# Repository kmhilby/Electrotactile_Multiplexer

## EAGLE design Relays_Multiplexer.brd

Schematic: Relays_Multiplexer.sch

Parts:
C1, C2: 10uF/6.3V; CAPC1005X55_SMD-0402
IC1, IC2: PCA9685; SOP65P650X110-28
J1, J3, J4: PTH VERT FEMALE; HDRVR2W64P254_1X2_558X254X850B
J2: 1x33 Molex Connector; _MOLEX-5025983393_FPC_PITCH-0.3MM
J5: 2x17 PTH RA FEMALE; 2X17-RA-FEMALE
R1, R2, R3, R4, R5, R6, R7, R8, R11, R12, R13, R14, R15, R16, R17, R18: 10K; RESC1005X35_SMD-0402
R9, R10, R19, R21, R22, R23, R24, R25, R26, R27, R28, R29, R30, R31, R32, R33, R34, R35, R36, R37, R38, R39, R40, R41, R42, R43, R44, R45, R46, R47, R48, R49: 1K; RESC1005X35_SMD-0402
RELAY1, RELAY2, RELAY3, RELAY4, RELAY5, RELAY6, RELAY7, RELAY8, RELAY10, RELAY11, RELAY12, RELAY13, RELAY14, RELAY15, RELAY16, RELAY17, RELAY18, RELAY19, RELAY20, RELAY21, RELAY22, RELAY23, RELAY24, RELAY25, RELAY26, RELAY27, RELAY28, RELAY29, RELAY30, RELAY31, RELAY32, RELAY33: SPST-NO 170mA 250V; SOP254P609X203-4

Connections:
AGND: J2.P$33 (33), J3.2
AVCC: J3.1, RELAY1.4, RELAY2.4, RELAY3.4, RELAY4.4, RELAY5.4, RELAY6.4, RELAY7.4, RELAY8.4, RELAY10.4, RELAY11.4, RELAY12.4, RELAY13.4, RELAY14.4, RELAY15.4, RELAY16.4, RELAY17.4, RELAY18.4, RELAY19.4, RELAY20.4, RELAY21.4, RELAY22.4, RELAY23.4, RELAY24.4, RELAY25.4, RELAY26.4, RELAY27.4, RELAY28.4, RELAY29.4, RELAY30.4, RELAY31.4, RELAY32.4, RELAY33.4
GND: C1.2, C2.2, IC1.14 (GND), IC1.25 (EXTCLK), IC2.14 (GND), IC2.25 (EXTCLK), J4.2, J5.33, J5.34, R1.2, R2.2, R3.2, R5.2, R6.2, R7.2, R8.2, R9.1, R10.1, R11.2, R12.2, R13.2, R14.2, R15.2, R16.2, R17.2, R19.1, R21.1, R22.1, R23.1, R24.1, R25.1, R26.1, R27.1, R28.1, R29.1, R30.1, R31.1, R32.1, R33.1, R34.1, R35.1, R36.1, R37.1, R38.1, R39.1, R40.1, R41.1, R42.1, R43.1, R44.1, R45.1, R46.1, R47.1, R48.1, R49.1
unnamed: IC1.23 (!OE), R3.1
unnamed: IC1.4 (A3), R7.1
unnamed: IC1.24 (A5), R11.1
unnamed: IC1.5 (A4), R8.1
unnamed: IC1.3 (A2), R6.1
unnamed: IC1.2 (A1), R5.1
unnamed: IC2.1 (A0), R12.1
unnamed: IC2.3 (A2), R13.1
unnamed: IC2.4 (A3), R14.1
unnamed: IC2.5 (A4), R15.1
unnamed: IC2.24 (A5), R16.1
unnamed: IC2.23 (!OE), R1.1
unnamed: J2.P$17 (17), RELAY18.3
unnamed: J2.P$16 (16), RELAY17.3
unnamed: J2.P$15 (15), RELAY16.3
unnamed: J2.P$14 (14), RELAY15.3
unnamed: J2.P$13 (13), RELAY14.3
unnamed: J2.P$12 (12), RELAY13.3
unnamed: J2.P$11 (11), RELAY12.3
unnamed: J2.P$10 (10), RELAY11.3
unnamed: J2.P$9 (9), RELAY4.3
unnamed: J2.P$8 (8), RELAY3.3
unnamed: J2.P$7 (7), RELAY2.3
unnamed: J2.P$6 (6), RELAY1.3
unnamed: J2.P$5 (5), RELAY5.3
unnamed: J2.P$4 (4), RELAY6.3
unnamed: J2.P$3 (3), RELAY7.3
unnamed: J2.P$2 (2), RELAY8.3
unnamed: J2.P$1 (1), RELAY10.3
unnamed: J2.P$18 (18), RELAY19.3
unnamed: J2.P$19 (19), RELAY20.3
unnamed: J2.P$20 (20), RELAY21.3
unnamed: J2.P$21 (21), RELAY22.3
unnamed: J2.P$22 (22), RELAY23.3
unnamed: J2.P$23 (23), RELAY24.3
unnamed: J2.P$24 (24), RELAY25.3
unnamed: J2.P$25 (25), RELAY26.3
unnamed: J2.P$26 (26), RELAY27.3
unnamed: J2.P$27 (27), RELAY28.3
unnamed: J2.P$28 (28), RELAY29.3
unnamed: J2.P$29 (29), RELAY30.3
unnamed: J2.P$30 (30), RELAY31.3
unnamed: J2.P$31 (31), RELAY32.3
unnamed: J2.P$32 (32), RELAY33.3
unnamed: R19.2, RELAY7.2
unnamed: R21.2, RELAY6.2
unnamed: R9.2, RELAY10.2
unnamed: R10.2, RELAY8.2
unnamed: R22.2, RELAY5.2
unnamed: R23.2, RELAY1.2
unnamed: R24.2, RELAY2.2
unnamed: R25.2, RELAY3.2
unnamed: R26.2, RELAY4.2
unnamed: R27.2, RELAY11.2
unnamed: R28.2, RELAY12.2
unnamed: R29.2, RELAY13.2
unnamed: R30.2, RELAY14.2
unnamed: R31.2, RELAY15.2
unnamed: R32.2, RELAY16.2
unnamed: R33.2, RELAY17.2
unnamed: R34.2, RELAY18.2
unnamed: R35.2, RELAY19.2
unnamed: R36.2, RELAY20.2
unnamed: R37.2, RELAY21.2
unnamed: R38.2, RELAY22.2
unnamed: R39.2, RELAY23.2
unnamed: R40.2, RELAY24.2
unnamed: R41.2, RELAY25.2
unnamed: R42.2, RELAY26.2
unnamed: R43.2, RELAY27.2
unnamed: R44.2, RELAY28.2
unnamed: R45.2, RELAY29.2
unnamed: R46.2, RELAY30.2
unnamed: R47.2, RELAY31.2
unnamed: R48.2, RELAY32.2
unnamed: R49.2, RELAY33.2
SCL: IC1.26 (SCL), IC2.26 (SCL), J1.2, R18.1
SDA: IC1.27 (SDA), IC2.27 (SDA), J1.1, R4.2
SW: IC1.18 (PWM11), J5.12, RELAY13.1
SW1: IC1.6 (PWM0), J5.1, RELAY10.1
SW2: IC1.7 (PWM1), J5.2, RELAY8.1
SW3: IC1.8 (PWM2), J5.3, RELAY7.1
SW4: IC1.9 (PWM3), J5.4, RELAY6.1
SW5: IC1.10 (PWM4), J5.5, RELAY5.1
SW6: IC1.11 (PWM5), J5.6, RELAY1.1
SW7: IC1.12 (PWM6), J5.7, RELAY2.1
SW8: IC1.13 (PWM7), J5.8, RELAY3.1
SW9: IC1.15 (PWM8), J5.9, RELAY4.1
SW10: IC1.16 (PWM9), J5.10, RELAY11.1
SW11: IC1.17 (PWM10), J5.11, RELAY12.1
SW13: IC1.19 (PWM12), J5.13, RELAY14.1
SW14: IC1.20 (PWM13), J5.14, RELAY15.1
SW15: IC1.21 (PWM14), J5.15, RELAY16.1
SW16: IC1.22 (PWM15), J5.16, RELAY17.1
SW17: IC2.6 (PWM0), J5.17, RELAY18.1
SW18: IC2.7 (PWM1), J5.18, RELAY19.1
SW19: IC2.8 (PWM2), J5.19, RELAY20.1
SW20: IC2.9 (PWM3), J5.20, RELAY21.1
SW21: IC2.10 (PWM4), J5.21, RELAY22.1
SW22: IC2.11 (PWM5), J5.22, RELAY23.1
SW23: IC2.12 (PWM6), J5.23, RELAY24.1
SW24: IC2.13 (PWM7), J5.24, RELAY25.1
SW25: IC2.15 (PWM8), J5.25, RELAY26.1
SW26: IC2.16 (PWM9), J5.26, RELAY27.1
SW27: IC2.17 (PWM10), J5.27, RELAY28.1
SW28: IC2.18 (PWM11), J5.28, RELAY29.1
SW29: IC2.19 (PWM12), J5.29, RELAY30.1
SW30: IC2.20 (PWM13), J5.30, RELAY31.1
SW31: IC2.21 (PWM14), J5.31, RELAY32.1
SW32: IC2.22 (PWM15), J5.32, RELAY33.1
VCC: C1.1, C2.1, IC1.1 (A0), IC1.28 (VCC), IC2.2 (A1), IC2.28 (VCC), J4.1, R2.1, R4.1, R17.1, R18.2

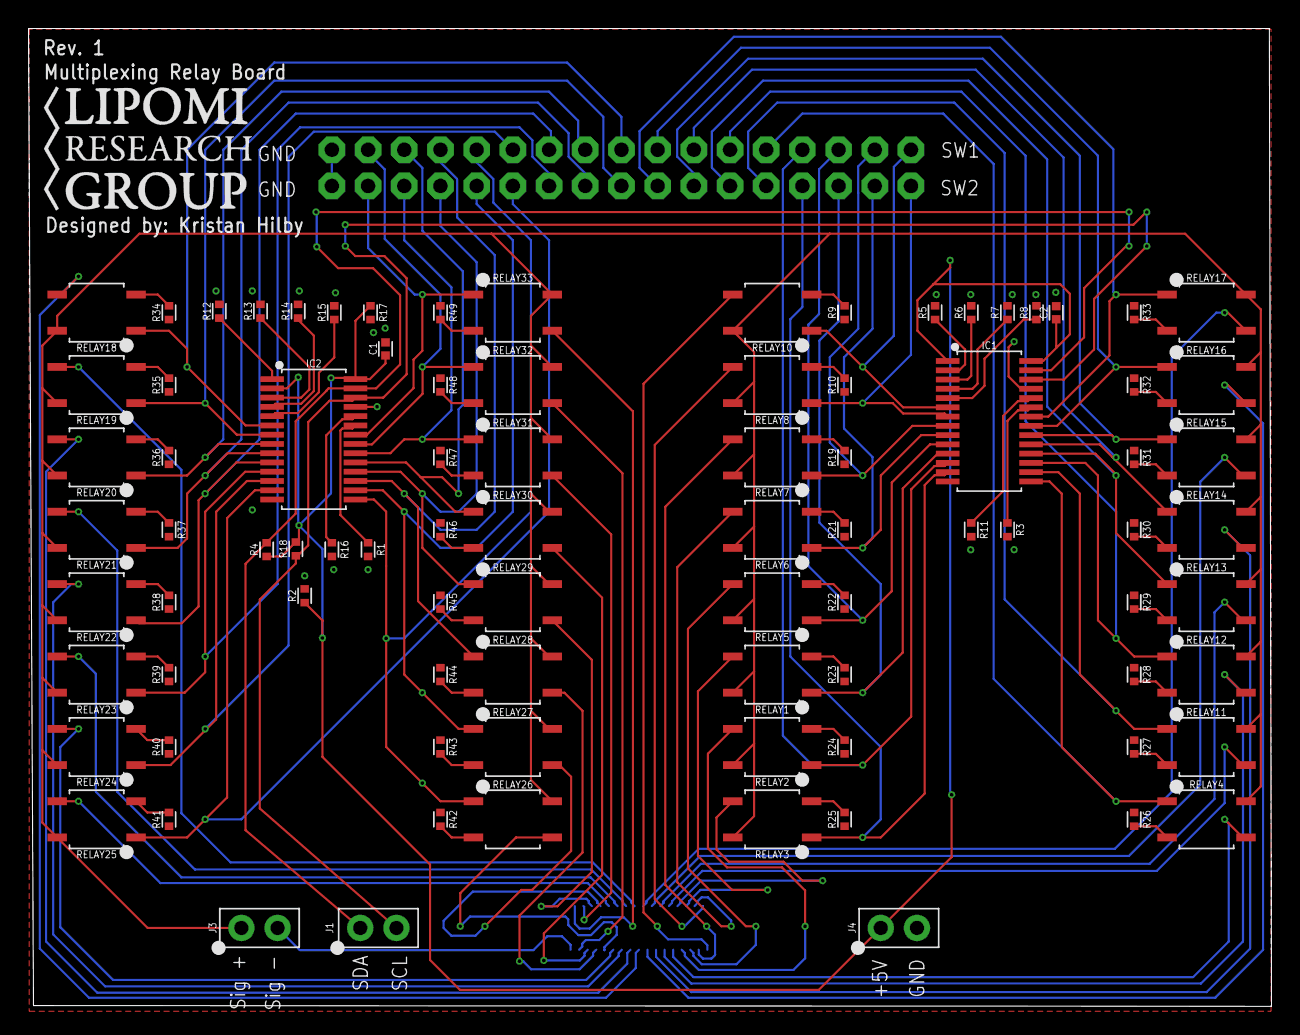
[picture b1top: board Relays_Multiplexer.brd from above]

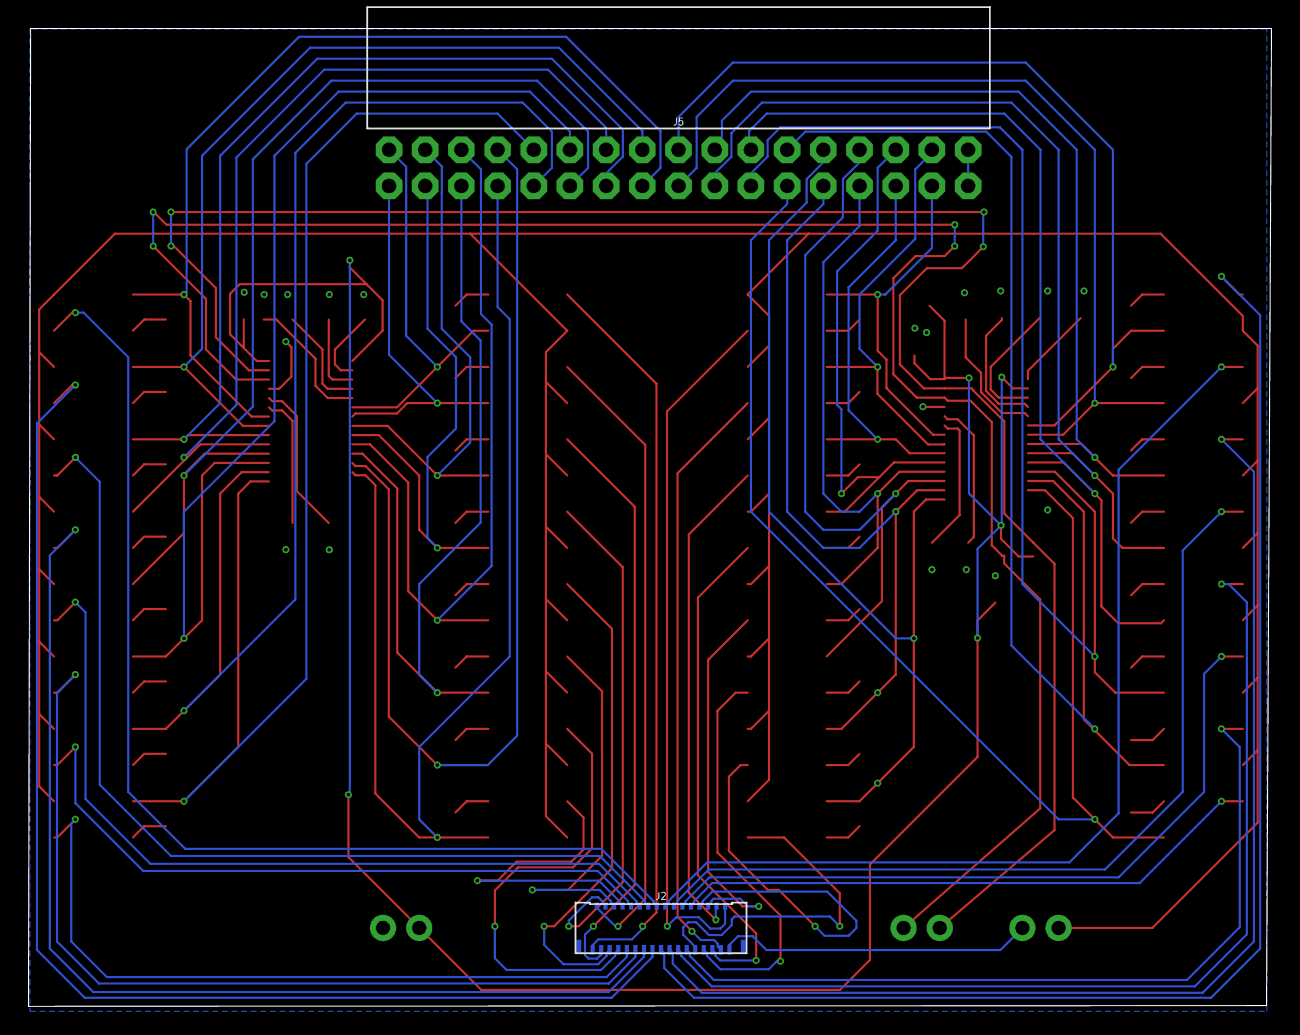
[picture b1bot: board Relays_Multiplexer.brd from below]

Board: 2 copper layers, 87.2 x 68.6 mm, 90 parts (2 on the bottom side), 114 nets.

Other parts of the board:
U$1: LRG-LOGO

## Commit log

2019-04-03 Board Schematic version 1 finished, board still WIP
2019-04-03 Killed routes >:) and rearranged board
2019-04-04 Board is fully routed, but kind of looks like shit
2019-04-09 Board is fully routed. We out here finishing things
2019-04-09 Board is fully routed. We out here finishing things part 2
2019-04-09 Updated some of the VCC connections.
2019-04-09 Added art and flexes
2019-04-30 Adding previously used arduino code
